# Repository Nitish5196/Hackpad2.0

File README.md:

# My Hackpad
this is my own hackpad i made with the help of (this guide)[https://hackpad.hackclub.com/] , it has 6 keys , 1 display and 1 rotary encoder and 16 LEDs . this was also my first hardware project . It was made using Kicad for PCB , Fusion360 for the case and  
### PCB

### CASE

### Bill of Materials (BOM)

| Component | Quantity | Total Cost (USD) | Vendor | Link |
|---|---:|---:|---|---|
| 1N4148 Diodes | 6 | $0.40 | Robocraze | [Link](https://robocraze.com/products/1n4148-diode-pack-of-10?_pos=1&_sid=930629372&_ss=r) |
| SK6812MINI-E LEDs | 16 | $3.00 | LCSC India | [Link](https://lcscindia.com/cart) |
| Oled display| 1 | $2.30 | Robocraze | [Link](https://lcscindia.com/cart) |
| Cherry MX Push Switches | 6 | $3.64 | NeoMacro| [Link](https://neomacro.in/products/cherry-mx-switches?srsltid=AYCX9vJ08EEjaJu5GJ2ko4Xj6fdsCfu17r3riEta1b7-DAo_B6HdMHyB) |
| Rotary Encoder | 1 | $0.80 | Robocraze | [Link](https://robocraze.com/products/ec11-15mm-rotary-encoder-module?variant=55020233588960&country=IN&currency=INR&utm_medium=product_sync&utm_source=google&utm_content=sag_organic&utm_campaign=sag_organic&utm_source=googleads&utm_medium=ppc&utm_campaign=24409531650&utm_content=_&utm_term=&campaignid=24409531650&adgroupid=&campaign=24409531650&gad_source=1&gad_campaignid=24420457345&gbraid=0AAAAADgHQvZC-h60bdXBKUkQIPFRYrdOH&gclid=Cj0KCQiAtvXXBhC2ARIsAJc8SUSweGKqkubisx5vRZHPyqdhR8OA86IxVbme_yRPPbRoMvKArEiaLdkaAodVEALw_wcB) |
| Seeed XIAO Module | 1 | $5.70 | Robocraze | [Link](https://robocraze.com/products/seeed-studio-xiao-rp2040-development-board?variant=47742255562976&country=IN&currency=INR&utm_medium=product_sync&utm_source=google&utm_content=sag_organic&utm_campaign=sag_organic&campaignid=23145906364&adgroupid=182236965810&keyword=&device=c&gad_source=1&gad_campaignid=23145906364&gbraid=0AAAAADgHQvY4QUT0OGkIS6mEjYK5fnyMf&gclid=Cj0KCQiAtvXXBhC2ARIsAJc8SURgu648XUCQUbSNj-s9D9Z02JxWU4MgDLShXVt9wNJsqGS0oTjPs9UaAmV9EALw_wcB) |
| Custom PCB | 1 | $9.60 | Robu | [Link](https://robu.in/product/online-pcb-manufacturing-service/) |
| 3D Printed Case | 1 | $8.00 | Printing Legion | [Link](https://printlegion.hackclub.com/) |
| **Total** | | **$33.44** | | |

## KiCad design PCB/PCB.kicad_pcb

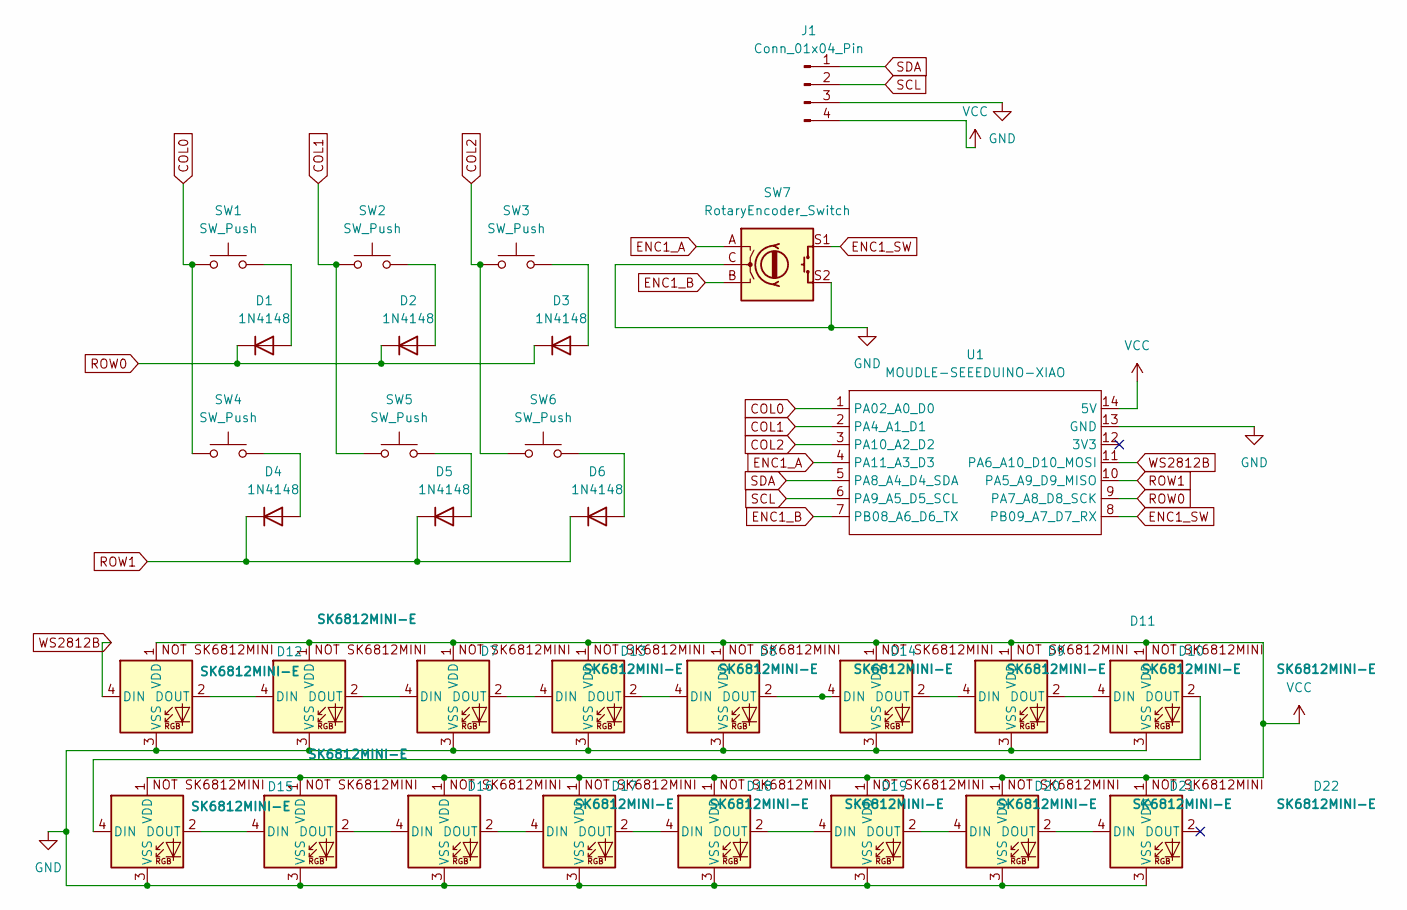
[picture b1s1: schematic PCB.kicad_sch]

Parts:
D1, D2, D3, D4, D5, D6: 1N4148; D_DO-35_SOD27_P7.62mm_Horizontal
D7, D8, D9, D10, D11, D12, D13, D14, D15, D16, D17, D18, D19, D20, D21, D22: SK6812MINI-E; SK6812MINI-E_fixed
J1: Conn_01x04_Pin; PinHeader_1x04_P2.54mm_Horizontal
SW1, SW2, SW3, SW4, SW5, SW6: SW_Push; SW_Cherry_MX_1.00u_PCB
SW7: RotaryEncoder_Switch; RotaryEncoder_Alps_EC11E-Switch_Vertical_H20mm
U1: MOUDLE-SEEEDUINO-XIAO; XIAO-Generic-Hybrid-14P-2.54-21X17.8MM

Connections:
COL0: SW1.1, SW4.1, U1.1 (PA02_A0_D0)
COL1: SW2.1, SW5.1, U1.2 (PA4_A1_D1)
COL2: SW3.1, SW6.1, U1.3 (PA10_A2_D2)
ENC1_A: SW7.A, U1.4 (PA11_A3_D3)
ENC1_B: SW7.B, U1.7 (PB08_A6_D6_TX)
ENC1_SW: SW7.S1, U1.8 (PB09_A7_D7_RX)
GND: D7.3 (VSS), D8.3 (VSS), D9.3 (VSS), D10.3 (VSS), D11.3 (VSS), D12.3 (VSS), D13.3 (VSS), D14.3 (VSS), D15.3 (VSS), D16.3 (VSS), D17.3 (VSS), D18.3 (VSS), D19.3 (VSS), D20.3 (VSS), D21.3 (VSS), D22.3 (VSS), J1.3, SW7.C, SW7.S2, U1.13 (GND)
unnamed: D1.2 (A), SW1.2
unnamed: D2.2 (A), SW2.2
unnamed: D3.2 (A), SW3.2
unnamed: D4.2 (A), SW4.2
unnamed: D5.2 (A), SW5.2
unnamed: D6.2 (A), SW6.2
unnamed: D9.2 (DOUT), D10.4 (DIN)
unnamed: D10.2 (DOUT), D11.4 (DIN)
unnamed: D11.2 (DOUT), D15.4 (DIN)
unnamed: D7.4 (DIN), D12.2 (DOUT)
unnamed: D7.2 (DOUT), D13.4 (DIN)
unnamed: D8.4 (DIN), D13.2 (DOUT)
unnamed: D8.2 (DOUT), D14.4 (DIN)
unnamed: D9.4 (DIN), D14.2 (DOUT)
unnamed: D15.2 (DOUT), D16.4 (DIN)
unnamed: D16.2 (DOUT), D17.4 (DIN)
unnamed: D17.2 (DOUT), D18.4 (DIN)
unnamed: D18.2 (DOUT), D19.4 (DIN)
unnamed: D19.2 (DOUT), D20.4 (DIN)
unnamed: D20.2 (DOUT), D21.4 (DIN)
unnamed: D21.2 (DOUT), D22.4 (DIN)
ROW0: D1.1 (K), D2.1 (K), D3.1 (K), U1.9 (PA7_A8_D8_SCK)
ROW1: D4.1 (K), D5.1 (K), D6.1 (K), U1.10 (PA5_A9_D9_MISO)
SCL: J1.2, U1.6 (PA9_A5_D5_SCL)
SDA: J1.1, U1.5 (PA8_A4_D4_SDA)
VCC: D7.1 (VDD), D8.1 (VDD), D9.1 (VDD), D10.1 (VDD), D11.1 (VDD), D12.1 (VDD), D13.1 (VDD), D14.1 (VDD), D15.1 (VDD), D16.1 (VDD), D17.1 (VDD), D18.1 (VDD), D19.1 (VDD), D20.1 (VDD), D21.1 (VDD), D22.1 (VDD), J1.4, U1.14 (5V)
WS2812B: D12.4 (DIN), U1.11 (PA6_A10_D10_MOSI)

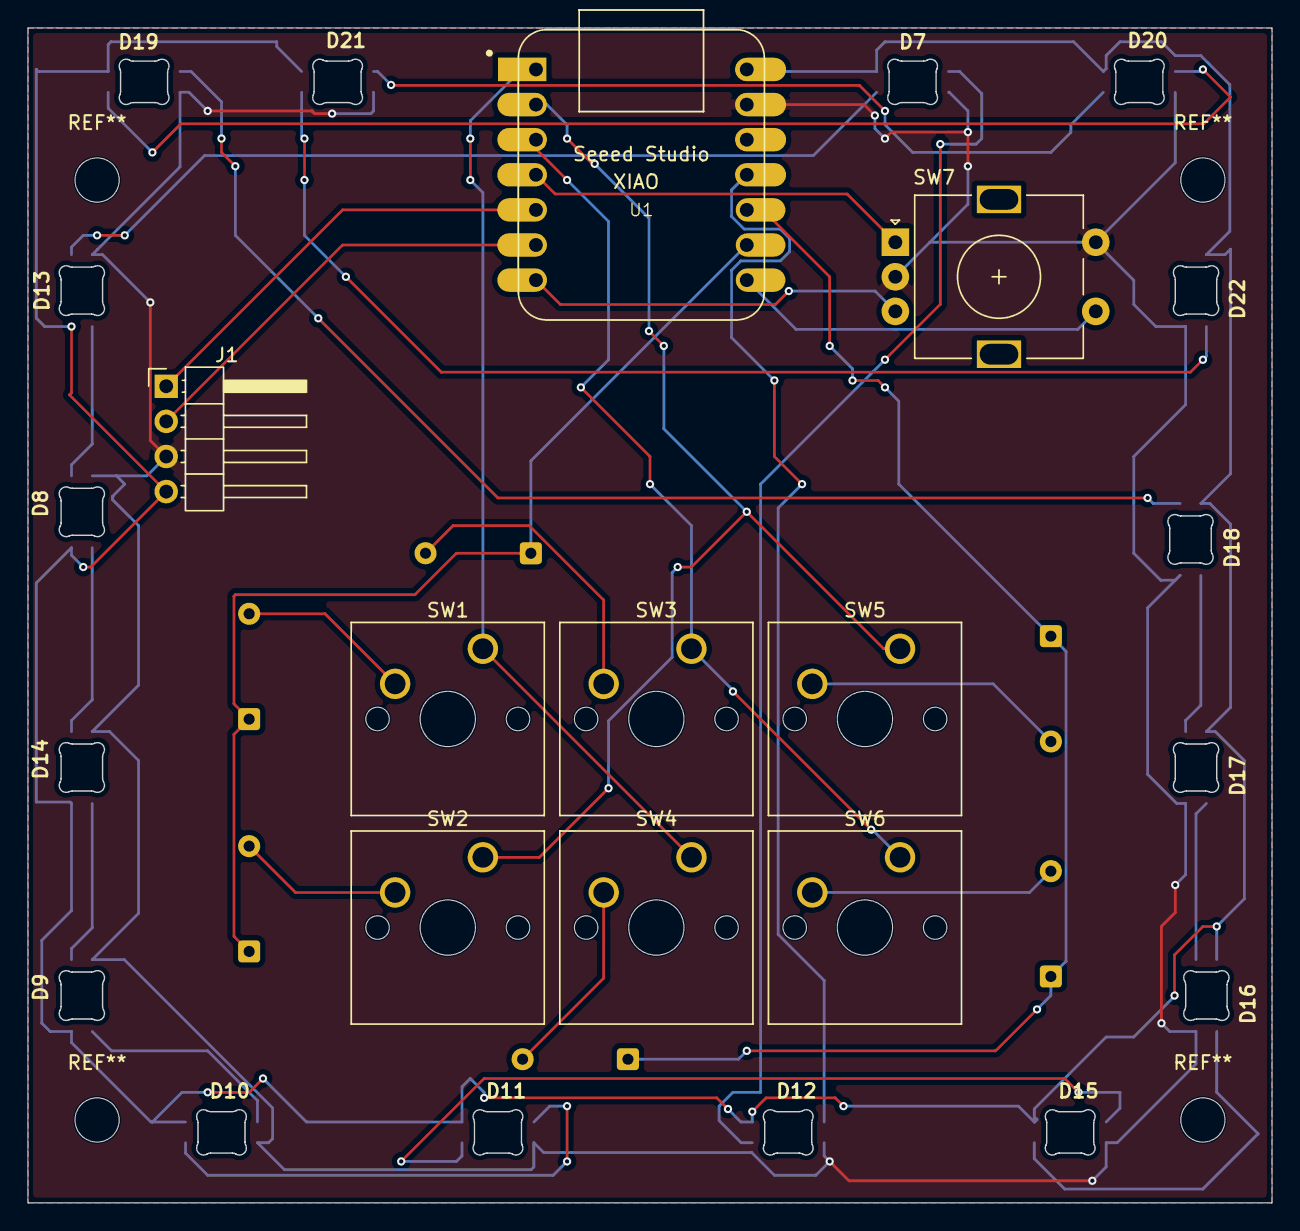
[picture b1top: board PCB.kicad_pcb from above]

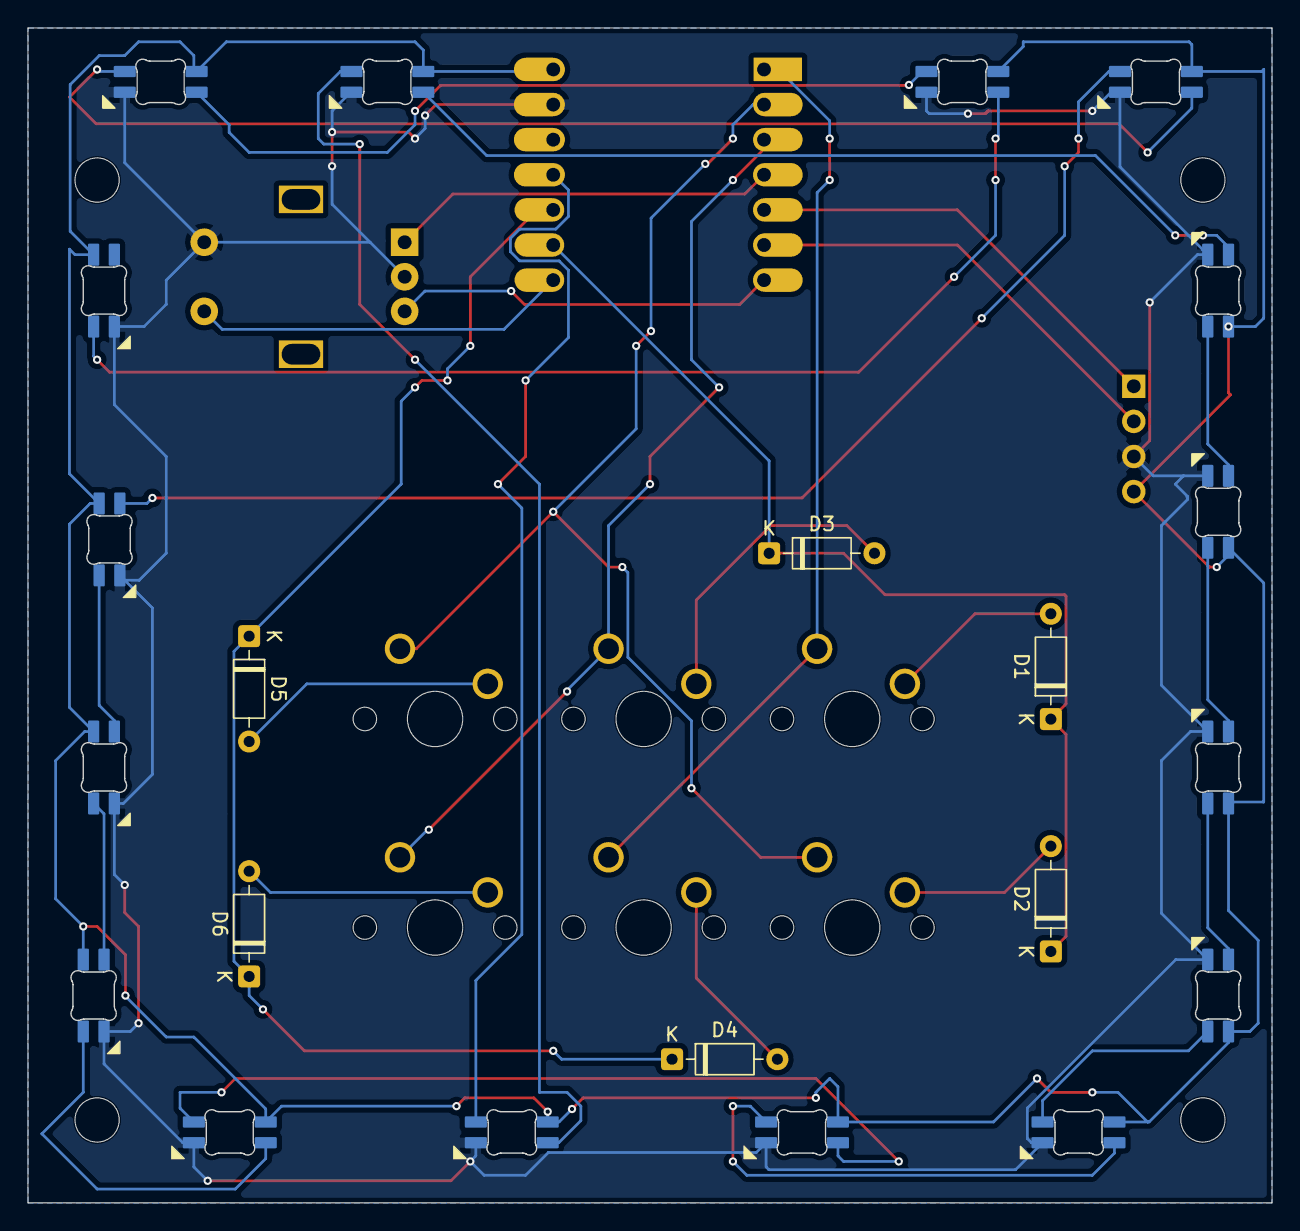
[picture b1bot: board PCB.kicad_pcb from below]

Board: 2 copper layers, 90.0 x 85.0 mm, 31 parts (6 on the bottom side), 34 nets.

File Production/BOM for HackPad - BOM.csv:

Id,Designator,Footprint,Quantity,Designation,Supplier and ref,Link,Price
1,"D1, D2, D3, D4, D5, D6",D_DO-35_SOD27_P7.62mm_Horizontal,6,1N4148,Robocraze,https://robocraze.com/products/1n4148-diode-pack-of-10?_pos=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,$0.40
2,"D7, D8, D9, D10, D11, D12, D13, D14, D15, D16, D17, D18, D19, D20, D21, D22",SK6812MINI-E_fixed,16,SK6812MINI-E,lcsc india,https://lcscindia.com/cart,$3.00
3,J1,PinHeader_1x04_P2.54mm_Horizontal,1,Conn_01x04_Pin,Robocraze,https://robocraze.com/products/0-91-inch-blue-oled-display-m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,$2.30
4,"SW1, SW2, SW3, SW4, SW5, SW6",SW_Cherry_MX_1.00u_PCB,6,SW_Push,NeoMacro,https://neomacro.in/products/cherry-mx-switches?srsltid=AYCX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,$3.64
5,SW7,RotaryEncoder_Alps_EC11E-Switch_Vertical_H20mm,1,RotaryEncoder_Switch,Robocraze,https://robocraze.com/products/ec11-15mm-rotary-encoder-modu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,$0.80
6,U1,XIAO-Generic-Hybrid-14P-2.54-21X17.8MM,1,MOUDLE-SEEEDUINO-XIAO,Robocraze,https://robocraze.com/products/seeed-studio-xiao-rp2040-deve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,$5.70
,PCB,,,,Robu,https://robu.in/product/online-pcb-manufacturing-service/,$9.60
,3D case,,,,Printing legion,https://printlegion.hackclub.com/,$8.00
,Total,,,,,,$33.44
